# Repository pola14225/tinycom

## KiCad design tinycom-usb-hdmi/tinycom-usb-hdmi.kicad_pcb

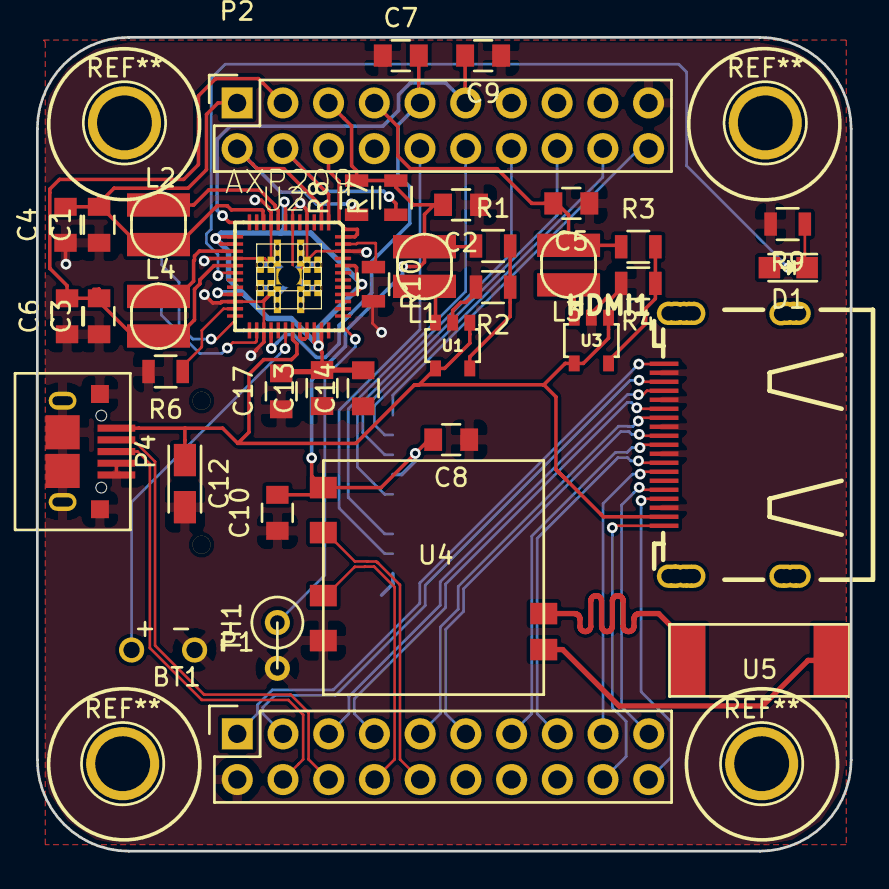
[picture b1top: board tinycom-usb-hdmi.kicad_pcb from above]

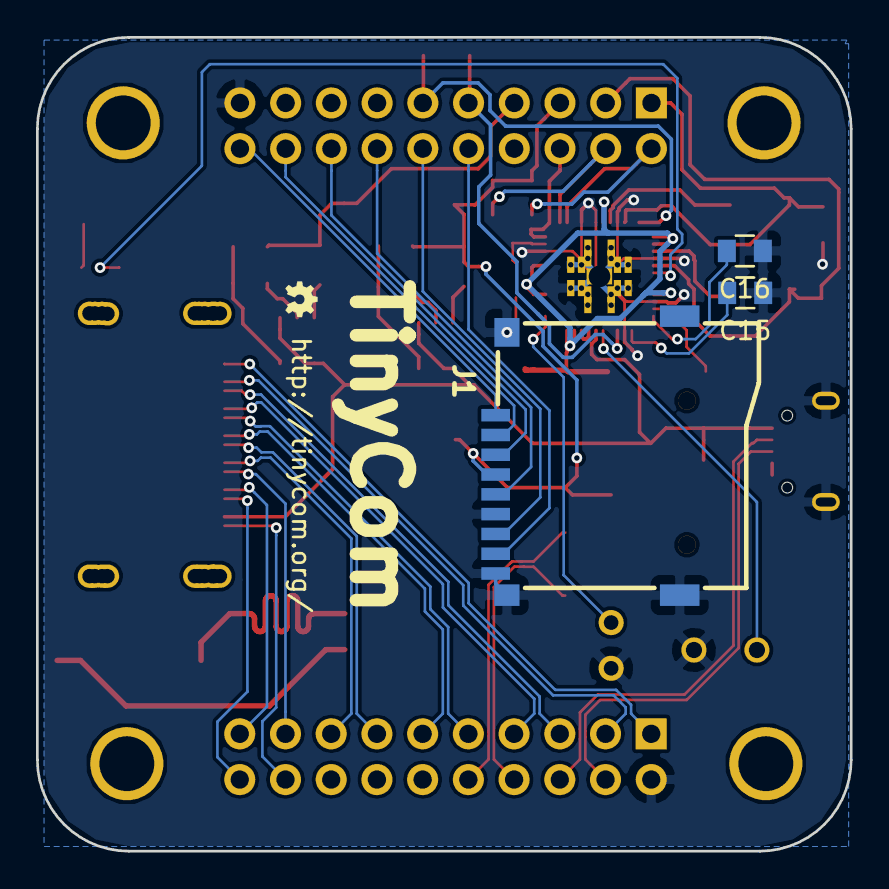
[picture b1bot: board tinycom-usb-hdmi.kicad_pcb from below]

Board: 2 copper layers, 45.2 x 45.2 mm, 42 parts (3 on the bottom side), 51 nets.

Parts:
BT1: Battery; ml1220-bat
C1, C2, C3, C4, C5, C6, C7, C8, C9, C10: C_Small; C_0805
C12: CP_Small; TantalC_SizeA_EIA-3216_Reflow
C13, C14, C17: 10uF; C_0805
C15, C16: 1uF; C_0805
D1: Led_Small; LED-0805
HDMI1: HDMI-SWM-19
J1: MICRO_SD_HINGE; SDCARD
L1, L2, L3, L4: SMD-INDUCTOR-2.2UH-20%-1.2A(0805); CD32
P1, P2: CONN_02X10; Socket_Strip_Straight_2x10
P4: USB_OTG; tc-USB_Micro-B
R1, R2, R3, R4: R_Small; R_0805
R6, R10: 200K; R_0805
R7, R8: 2.2K; R_0805
R9: 300; R_0805
TH1: THERMISTOR; R1
U1, U3: SY8008BAAC; SOT23-5_Opendous
U2: AXP209; ax209
U4: RTL8188
U5: rainsun-antenna

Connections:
+5V: C12.1, HDMI1.18, P4.1, U1.1, U1.4, U2.31, U3.1, U3.4
GND: BT1.2, C1.1, C2.1, C3.1, C4.1, C5.1, C6.1, C7.1, C8.1, C9.1, C10.1, C12.2, C13.1, C14.1, C15.1, C16.1, C17.1, HDMI1.2, HDMI1.5, HDMI1.8, HDMI1.11, HDMI1.17, J1.6, J1.9, J1.10, J1.11, J1.12, P1.2, P2.19, P4.4, P4.5, P4.6, R2.2, R4.2, R6.2, R9.2, R10.2, TH1.2, U1.2, U2.4, U2.6, U2.9, U2.16, U2.22, U2.27, U2.46, U2.N1, U3.2, U4.1
HCEC: HDMI1.13, P1.17
HCSL: HDMI1.15, P1.19
HHPD: HDMI1.19, P1.18
HSDA: HDMI1.16, P1.20
HTX0_N: HDMI1.9, P1.11
HTX0_P: HDMI1.7, P1.9
HTX1_N: HDMI1.6, P1.7
HTX1_P: HDMI1.4, P1.5
HTX2_N: HDMI1.3, P1.3
HTX2_P: HDMI1.1, P1.1
HTXC_N: HDMI1.12, P1.15
HTXC_P: HDMI1.10, P1.13
IPSOUT: C13.2, C14.2, C17.2, U2.7, U2.13, U2.14, U2.21, U2.34, U2.35, U2.40, U2.44
NMI_N: P2.6, U2.48
unnamed: BT1.1, U2.30
unnamed: C15.2, U2.26
unnamed: C16.2, U2.24
unnamed: D1.1, R9.1
unnamed: D1.2, U2.18
unnamed: L1.1, U1.3
unnamed: L2.1, U2.8
unnamed: L3.1, U3.3
unnamed: L4.1, U2.15
unnamed: R1.2, R2.1, U1.5
unnamed: R3.2, R4.1, U3.5
unnamed: R6.1, U2.23
unnamed: R10.1, U2.47
unnamed: TH1.1, U2.37
unnamed: U2.32, U2.33
unnamed: U4.5, U5.2
unnamed: U4.6, U5.1
SDC0_CLK: J1.5, P2.14
SDC0_CMD: J1.3, P2.16
SDC0_D0: J1.7, P2.12
SDC0_D1: J1.8, P2.10
SDC0_D2: J1.1, P2.20
SDC0_D3: J1.2, P2.18
TWI0_SCK: P2.2, R8.1, U2.2
TWI0_SDA: P2.4, R7.1, U2.1
UD0_N: P1.6, P4.2
UD0_P: P1.4, P4.3
UD1_N: P1.10, U4.3
UD1_P: P1.8, U4.2
VCC_12_CPU: C1.2, C4.2, L2.2, P2.1, U2.10
VCC_12_INT: C3.2, C6.2, L4.2, P2.3, U2.17
VCC_13_RTC: C7.2, P2.9, U2.28
VCC_15: C5.2, L3.2, P2.7, R3.1
VCC_30_ANL: C9.2, P2.11, U2.12
VCC_33: C2.2, C8.2, C10.2, J1.4, L1.2, P2.5, R1.1, R7.2, R8.2, U4.4
